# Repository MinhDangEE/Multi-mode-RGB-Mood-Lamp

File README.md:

# Multi-Mode RGB Mood Lamp with Auto-Off Timer on STM32F103C8T6

This project implements an embedded ambient lighting system using the STM32F103C8T6 (ARM Cortex-M3) microcontroller. It combines 3-channel 16-bit Timer PWM color blending, real-time potentiometer brightness regulation via ADC, a push-button auto-off countdown timer, an SSD1306 OLED interface, and a browser-based control dashboard. The dashboard reaches the lamp either directly over USB (Web Serial) or **from anywhere on the Internet** through an ESP32-S3 that bridges MQTT to the STM32 UART at 115200 baud.

### ▶ Live control panel

**https://web-tikoocs-projects.vercel.app/?id=moodlamp-a3781afd**

The `?id=` query is required — it tells the page which lamp to address. The
lamp only answers while its ESP32-S3 is powered and on WiFi; the panel shows
**Đèn online** or **Đèn đang offline** in the top-right corner. You do not need
to be on the same network as the lamp.

---

## Table of Contents

1. [System Overview](#1-system-overview)
2. [Hardware Bill of Materials](#2-hardware-bill-of-materials)
3. [System Flowchart & Control Logic](#3-system-flowchart--control-logic)
4. [Hardware Pinout & Peripheral Mapping](#4-hardware-pinout--peripheral-mapping)
5. [Operational Lighting Modes](#5-operational-lighting-modes)
6. [Auto-Off Countdown Timer](#6-auto-off-countdown-timer)
7. [Web Control & UART Protocol](#7-web-control--uart-protocol)
8. [Internet Control via ESP32-S3](#8-internet-control-via-esp32-s3)
9. [Demo Video](#9-demo-video)
10. [Limitations and Future Improvements](#10-limitations-and-future-improvements)
11. [Authors](#11-authors)

---

## 1. System Overview

The firmware leverages hardware peripherals of the STM32F103C8T6 MCU to drive a common-cathode RGB LED and manage interactive controls:

TIM3 generates 1 kHz PWM across channels 1, 2, and 3 (PA6, PA7, PB0) for independent color mixing. Analog input from a 10k potentiometer on PA1 is converted through ADC1 to scale total luminous output from 0% to 100%. User control is handled via two tactile buttons: a mode toggle on PB12, and a timer button on PB13 that adds 5 minutes per press up to a 30-minute cap. Both use internal pull-ups with 300 ms software debouncing. Status information is rendered on a 128x64 SSD1306 OLED module over software I2C.

---

## 2. Hardware Bill of Materials

The complete hardware prototype is constructed using the following components and breakout modules:

| Component / Module | Specification / Model | Quantity | Role in System |
| :--- | :--- | :---: | :--- |
| **Microcontroller Board** | STM32F103C8T6 Blue Pill (ARM Cortex-M3, 72 MHz, 64KB Flash) | 1 | Master embedded processing unit |
| **RGB LED Module** |  Common-Cathode RGB LED Breakout Module | 1 | 3-channel PWM mood light emitter |
| **Timer Push Button** | 6x6mm Tactile Momentary Push Button | 1 | Adds 5 minutes to the auto-off timer per press |
| **WiFi Bridge Board** | ESP32-S3 DevKitC-1 (Xtensa LX7, WiFi 2.4 GHz) | 1 | Relays MQTT commands from the Internet to the STM32 UART |
| **OLED Display Module** | 0.96 inch SSD1306 I2C OLED Module (128x64 pixels, Blue/White) | 1 | Real-time status, mode, and countdown visualization |
| **Potentiometer** | 10k Linear Rotary Potentiometer (B10K) | 1 | Analog 0% to 100% master brightness regulator |
| **Mode Push Button** | 6x6mm Tactile Momentary Push Button | 1 | External hardware mode toggle trigger |
| **USB-to-UART Adapter** | CP2102 USB to Serial TTL Adapter | 1 | Bidirectional PC/Web Serial interface (115200 baud) |
| **Debugger / Programmer** | ST-Link V2 USB Dongle | 1 | SWD firmware flashing and hardware debugging |
| **Prototyping Accessories** | Solderless Breadboard and Jumper Wires | 1 set | Circuit interconnects and power distribution |

---

## 3. System Flowchart & Control Logic

The execution flow, mode transition logic, potentiometer ADC brightness mapping, and countdown timer routine are illustrated in the architecture flowchart below:

<div align="center">
  
</div>

---

## 4. Hardware Pinout & Peripheral Mapping

| Device / Module | Module Pin | STM32 Pin | Peripheral Function | Electrical Role |
| :--- | :--- | :--- | :--- | :--- |
| RGB LED Module | Red Channel (R) | PA6 | TIM3_CH1 | 1 kHz PWM Output |
| | Green Channel (G) | PA7 | TIM3_CH2 | 1 kHz PWM Output |
| | Blue Channel (B) | PB0 | TIM3_CH3 | 1 kHz PWM Output |
| | Common Ground (-) | GND | Ground | Common Cathode Reference |
| 10k Potentiometer | Wiper Pin | PA1 | ADC1_IN1 | Analog Voltage Input (0V to 3.3V) |
| | Outer Rails | 3.3V / GND | Power Rails | Voltage Divider Reference |
| Timer Button | Tactile Switch | PB13 | EXTI13 | Falling-Edge, +5 min per press |
| Mode Button | Tactile Switch | PB12 | EXTI12 | Falling-Edge Mode Toggle |
| SSD1306 OLED Module | SCL | PB6 | GPIO Output PP | Software I2C Clock |
| | SDA | PB7 | GPIO Output PP | Software I2C Data |
| | Power (VCC / GND)| 3.3V / GND | Power Rails | Module Display Power |
| USB-UART Bridge | TXD / RXD | PA10 / PA9 | USART1 (RX/TX) | 115200 8N1 Serial Protocol |
| ESP32-S3 Bridge | GPIO17 (TX) | PA10 | USART1_RX | Crossed TX-to-RX, 3.3V logic |
| | GPIO18 (RX) | PA9 | USART1_TX | Crossed RX-to-TX, 3.3V logic |
| | GND | GND | Ground | Mandatory common ground reference |
| ST-Link V2 | SWDIO / SWCLK | PA13 / PA14 | SWD Debug | Firmware Flash & Debug |

---

## 5. Operational Lighting Modes

The lamp implements five discrete operational states:

1. **Solid White:** Drives Red, Green, and Blue channels at full duty cycle. Overall luminous intensity is dynamically scaled by the PA1 potentiometer.
2. **Breathing White:** Modulates intensity through a 3000 ms periodic cycle applying a non-linear Gamma 2.2 curve (`Duty = MaxBright * Progress^2.2`) to match human eye lightness perception.
3. **Rainbow Spectrum:** Cycles through six chromatic spectrum zones (Red -> Yellow -> Green -> Cyan -> Blue -> Magenta -> Red) over a 6000 ms period using linear PWM crossfading without color jumping.
4. **Custom RGB:** Directly applies color coordinates transmitted over UART from the Web Serial palette.
5. **Sleep / Standby:** Sets all PWM compare registers to zero, turning off the LED completely upon manual selection or timer expiration.

---

## 6. Auto-Off Countdown Timer

Each press of the timer button (PB13) adds 5 minutes to the countdown, saturating at a 30-minute ceiling. The button uses the internal pull-up with 300 ms software debouncing, so no external resistor is required.

A background tick decrements the remaining time once per second. The tick accumulates its reference (`timer_last_tick += 1000`) instead of reassigning it from the current millisecond count, which keeps the countdown from drifting over long durations. When the counter reaches zero, the firmware automatically switches to Sleep Mode (Mode 0) and blanks the LED output. Remaining time is continuously updated on the OLED display and echoed over UART.

---

## 7. Web Control & UART Protocol

The dashboard in [`web/`](web/) is a single dependency-free HTML file. It reaches the lamp two ways and picks one automatically at load time:

- **MQTT** — when opened with `?id=<DEVICE_ID>`, it talks to the ESP32-S3 bridge over the Internet (see section 8).
- **Web Serial** — otherwise it asks for a COM port and drives a USB-UART adapter directly.

Either way it sends the **same bytes**, so the STM32 firmware is unaware of which path was used. The interface offers a native color picker, R/G/B sliders, mode preset buttons, and a line-buffered device log.

| Command Packet | Target Action | Example / Details |
| :--- | :--- | :--- |
| `1\n` or `w\n` | Switch to Solid White | Constant white illumination |
| `2\n` or `b\n` | Switch to Breathing White | Gamma 2.2 breathing cycle |
| `3\n` or `r\n` | Switch to Rainbow Spectrum | 6-phase chromatic crossfade |
| `4\n` or `c\n` | Switch to Custom RGB | Uses current custom RGB registers |
| `0\n` or `s\n` | Switch to Sleep Mode | Turns off PWM channels |
| `n\n` or `Space` | Next Mode | Cycles sequentially through states |
| `C:R,G,B\n` | Set Custom RGB Coordinates | Example: `C:255,120,40\n` |
| `#RRGGBB\n` | Set Custom Hex Color | Example: `#FF7828\n` |

Because the firmware parses **one character at a time**, the multi-character packets (`C:R,G,B` and `#RRGGBB`) are only honoured by builds that add a string accumulator to `HAL_UART_RxCpltCallback()`.

To drive the lamp over USB, open `web/index.html` in Chrome or Edge, click Connect STM32 and choose the COM port. For Internet control, see the next section.

### Bench control over SWD

When a debugger is attached, [`tools/`](tools/) drives the lamp without any UART link by writing straight into MCU RAM through OpenOCD:

```bash
./tools/lamp.sh solid | breath | rainbow | sleep | next
./tools/lamp.sh status      # mode, PWM duty, ADC, timer
./tools/lamp.sh monitor     # continuous view, replaces a UART terminal
./tools/lamp.sh timer 5     # set auto-off, 0 cancels
```

The scripts resolve variable addresses from `build/STM32.elf` at run time with `arm-none-eabi-nm`, so they keep working after a rebuild moves things around.

---

## 8. Internet Control via ESP32-S3

The lamp sits behind a home router with a private address, so nothing on the Internet can reach it directly — port forwarding and a static IP would be needed, and neither is practical. Instead **both sides dial out** to a public MQTT broker and hold the connection open:

```
browser (HTTPS) ─┐
                 ├─→ broker.emqx.io ──→ ESP32-S3 ──UART──→ STM32F103
     ESP32-S3 ───┘                                          (the lamp)
         ↑ outbound only, traverses NAT
```

The two devices never learn each other's address; they share a mailbox. No port forwarding, no static IP, and the operator does **not** need to be on the same WiFi as the lamp.

The ESP32 does **not** control the LED. It relays bytes between MQTT and UART — an infinitely long USB-UART cable — and forwards exactly the characters the existing firmware already understands, which is why **no STM32 source change was required**. Lines the STM32 prints travel back the same way and appear in the dashboard log.

Firmware lives in [`esp32_mood_lamp/`](esp32_mood_lamp/) (PlatformIO + Arduino). Before flashing, copy `include/config.example.h` to `include/config.h` and fill in the WiFi credentials and a hard-to-guess `DEVICE_ID`; that file is git-ignored because it holds a password. Note the ESP32-S3 joins **2.4 GHz networks only**.

```bash
cd esp32_mood_lamp && pio run -t upload && pio device monitor
```

Then open the dashboard with the matching id:

```
https://web-tikoocs-projects.vercel.app/?id=<DEVICE_ID>
```

> The broker is a free public one: traffic is not privately encrypted and anyone who guesses the `DEVICE_ID` can drive the lamp. Acceptable for decorative lighting — not for locks or anything hazardous.

---

## 9. Demo Video

Functional testing footage, hardware validation, potentiometer brightness control, encoder timer countdown, and web serial communication can be reviewed here:

[Demo Video](https://drive.google.com/drive/folders/1vPH_NVBRHYjKIKNvcpQxKeFuqSAPMJKs?usp=sharing)

---

## 10. Limitations and Future Improvements

While the current system operates reliably, several hardware and software limitations offer clear opportunities for future development:

1. **State Persistence:** Current configuration parameters (active mode, custom RGB values, timer states) reside in volatile RAM and reset upon power loss. Emulating EEPROM in Flash memory (internal Flash pages) would enable persistent state recovery across reboot cycles.
2. **Wireless Connectivity — implemented:** an ESP32-S3 now bridges MQTT to the UART, so the lamp is reachable from anywhere (section 8). Remaining work: move off the public broker onto an authenticated one, and expose the lamp to Home Assistant via MQTT discovery.
3. **Command Set:** the firmware parses a single character per interrupt, so custom colour, brightness and timer cannot be driven from the web yet. Adding a string accumulator to `HAL_UART_RxCpltCallback()` plus a `STATE_CUSTOM` would close the gap.
4. **Acoustic / Sound Sync Mode:** Adding an analog electret microphone with an operational amplifier or an I2S digital microphone (e.g., INMP441) would allow hardware FFT analysis on the STM32 to create audio-reactive music visualization.
5. **Power Management:** In Sleep Mode, the microcontroller remains in full run mode with peripherals active. Implementing STM32 Stop Mode or Standby Mode with EXTI wakeup would significantly reduce idle current consumption for battery-powered operation.

---

## 11. Authors

- Dang Quang Minh
- Duong Minh Trong
- Ho Thanh Nhan

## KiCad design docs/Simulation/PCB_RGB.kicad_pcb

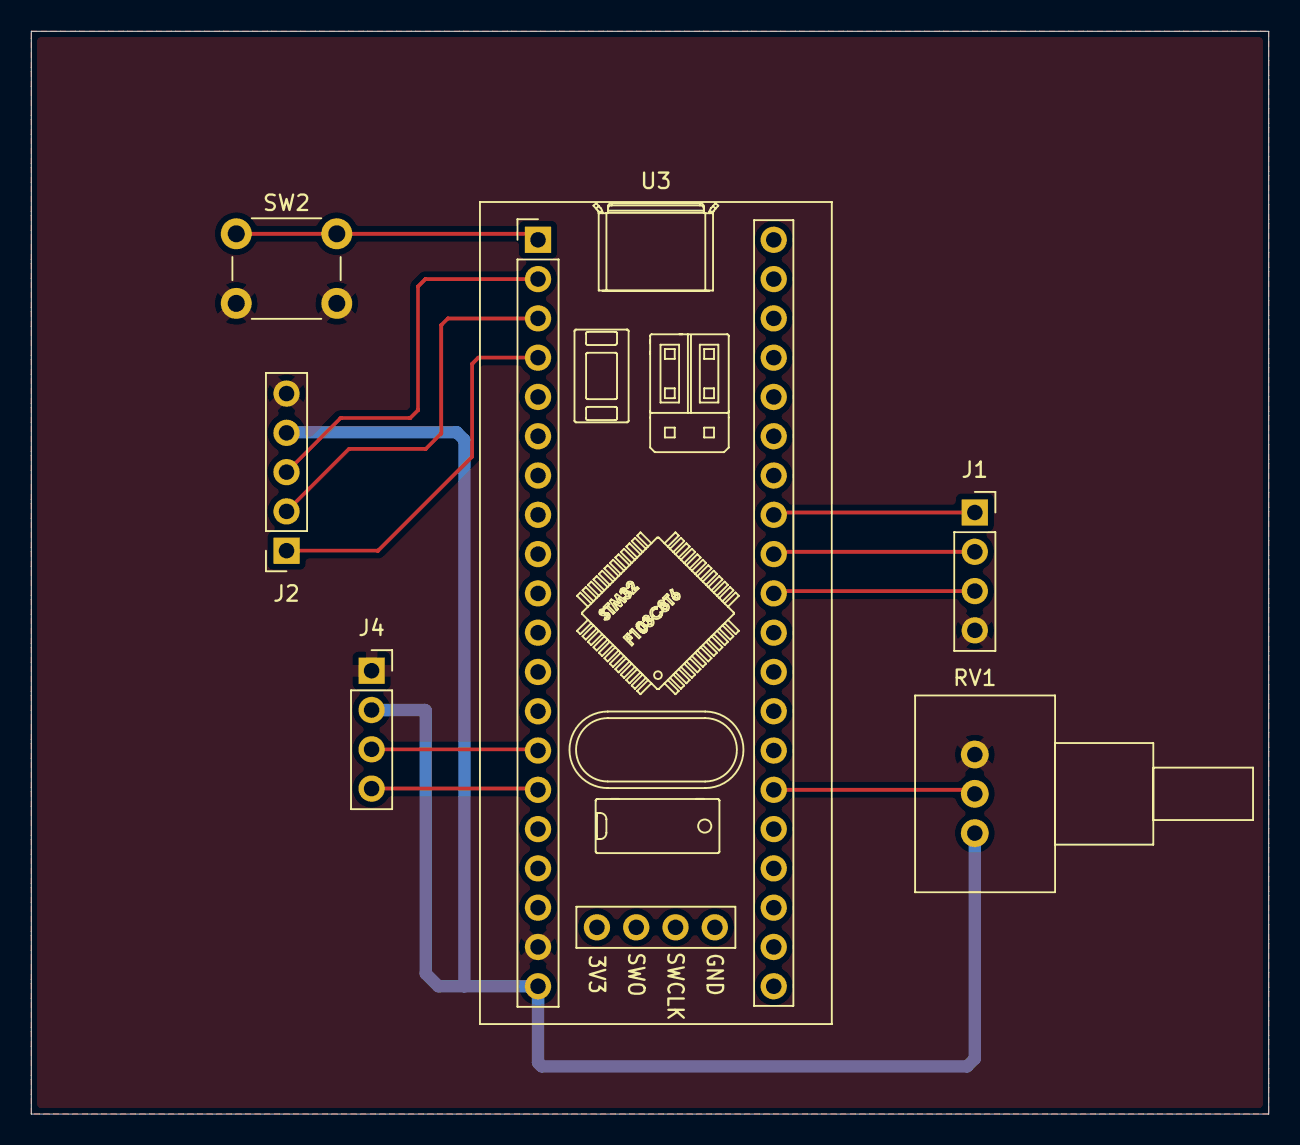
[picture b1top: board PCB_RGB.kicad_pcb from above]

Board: 2 copper layers, 80.0 x 70.0 mm, 6 parts (0 on the bottom side), 12 nets.

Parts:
J1, J4: Conn_01x04_Socket; PinSocket_1x04_P2.54mm_Vertical
J2: Conn_01x05_Socket; PinSocket_1x05_P2.54mm_Vertical
RV1: 10K; Potentiometer_Vishay_148-149_Single_Horizontal
SW2: MODE; SW_PUSH_6mm_H5mm
U3: YAAJ_BluePill_Part_Like_SWD_Breakout; YAAJ_BluePill_SWD_1

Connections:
/3V3: J2.4, J4.2, RV1.1, U3.20 (3V3)
/ADC_POT: RV1.2, U3.26 (PA1)
/BTN_MODE: SW2.1, U3.1 (PB12)
/CLK: J2.1, U3.4 (PB15)
/DT: J2.2, U3.3 (PB14)
/GND: J1.4, J2.5, J4.1, RV1.3, SW2.2, U3.19 (GND)
/I2C_SCL: J4.3, U3.14 (PB6)
/I2C_SDA: J4.4, U3.15 (PB7)
/PWM_B: J1.1, U3.33 (PB0)
/PWM_G: J1.2, U3.32 (PA7)
/PWM_R: J1.3, U3.31 (PA6)
/SW: J2.3, U3.2 (PB13)

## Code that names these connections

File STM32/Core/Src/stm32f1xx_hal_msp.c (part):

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
    __HAL_RCC_GPIOA_CLK_ENABLE();
    /**ADC1 GPIO Configuration
    PA1     ------> ADC1_IN1
    */
    GPIO_InitStruct.Pin = GPIO_PIN_1;
    GPIO_InitStruct.Mode = GPIO_MODE_ANALOG;
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    __HAL_RCC_ADC1_CLK_DISABLE();

    /**ADC1 GPIO Configuration
    PA1     ------> ADC1_IN1
    */
    HAL_GPIO_DeInit(GPIOA, GPIO_PIN_1);

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
    __HAL_RCC_GPIOB_CLK_ENABLE();
    /**I2C1 GPIO Configuration
    PB6     ------> I2C1_SCL
    PB7     ------> I2C1_SDA
    */
    GPIO_InitStruct.Pin = GPIO_PIN_6|GPIO_PIN_7;
    GPIO_InitStruct.Mode = GPIO_MODE_AF_OD;
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    __HAL_RCC_I2C1_CLK_DISABLE();

    /**I2C1 GPIO Configuration
    PB6     ------> I2C1_SCL
    PB7     ------> I2C1_SDA
    */
    HAL_GPIO_DeInit(GPIOB, GPIO_PIN_6);

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    __HAL_RCC_GPIOA_CLK_ENABLE();
    __HAL_RCC_GPIOB_CLK_ENABLE();
    /**TIM3 GPIO Configuration
    PA6     ------> TIM3_CH1
    PA7     ------> TIM3_CH2
    PB0     ------> TIM3_CH3
    */
    GPIO_InitStruct.Pin = GPIO_PIN_6|GPIO_PIN_7;
    GPIO_InitStruct.Mode = GPIO_MODE_AF_PP;
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
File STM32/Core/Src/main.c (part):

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  ssd1306_UpdateScreen();

  // Bật 3 kênh PWM của TIM3 cho LED RGB
  HAL_TIM_PWM_Start(&htim3, TIM_CHANNEL_1); // Kênh Đỏ (PA6)
  HAL_TIM_PWM_Start(&htim3, TIM_CHANNEL_2); // Kênh Xanh lá (PA7)
  HAL_TIM_PWM_Start(&htim3, TIM_CHANNEL_3); // Kênh Xanh dương (PB0)

  char startup_msg[] = "He thong Den RGB Mood Lamp san sang!\r\n";
  HAL_UART_Transmit(&huart1, (uint8_t*)startup_msg, strlen(startup_msg), 100);
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  __HAL_RCC_GPIOA_CLK_ENABLE();
  __HAL_RCC_GPIOB_CLK_ENABLE();

  /*Configure GPIO pins : PB12 PB13 */
  GPIO_InitStruct.Pin = GPIO_PIN_12|GPIO_PIN_13;
  GPIO_InitStruct.Mode = GPIO_MODE_IT_FALLING;
  GPIO_InitStruct.Pull = GPIO_PULLUP;
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    static uint32_t last_pb12_time = 0;
    static uint32_t last_pb13_time = 0;

    // Xử lý nút Đổi chế độ (PB12) - Thêm thuật toán Chống dội (Debounce 200ms)
    if (GPIO_Pin == GPIO_PIN_12) { 
        if ((current_time - last_pb12_time) > 200) {
            // Xác nhận lại nút vẫn đang được nhấn (Mức 0/RESET vì kích cạnh xuống)
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        }
    }
    
    // Xử lý nút Hẹn giờ (PB13) - Thêm thuật toán Chống dội (Debounce 200ms)
    if (GPIO_Pin == GPIO_PIN_13) { 
        if ((current_time - last_pb13_time) > 200) {
            // Xác nhận lại nút vẫn đang được nhấn (Mức 0/RESET)
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

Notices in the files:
STM32/Core/Src/main.c:
Copyright (c) 2026 STMicroelectronics.
All rights reserved.
This software is licensed under terms that can be found in the LICENSE file
